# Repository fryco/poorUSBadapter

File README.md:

# poorUSBadapter
V-USB hardware adapter for `poorDuino`

## Features
* Comaptible with `poorDuino` and another Arduino-flavoured boards (pin compatibility with Arduino UNO R3 is kept),
* Differential pair routing is apllied to `D+` and `D-` signal traces,
* Bootloader button included into design.

## Resources
1. V-USB https://www.obdev.at/products/vusb/index.html
2. metaboard https://metalab.at/wiki/Metaboard

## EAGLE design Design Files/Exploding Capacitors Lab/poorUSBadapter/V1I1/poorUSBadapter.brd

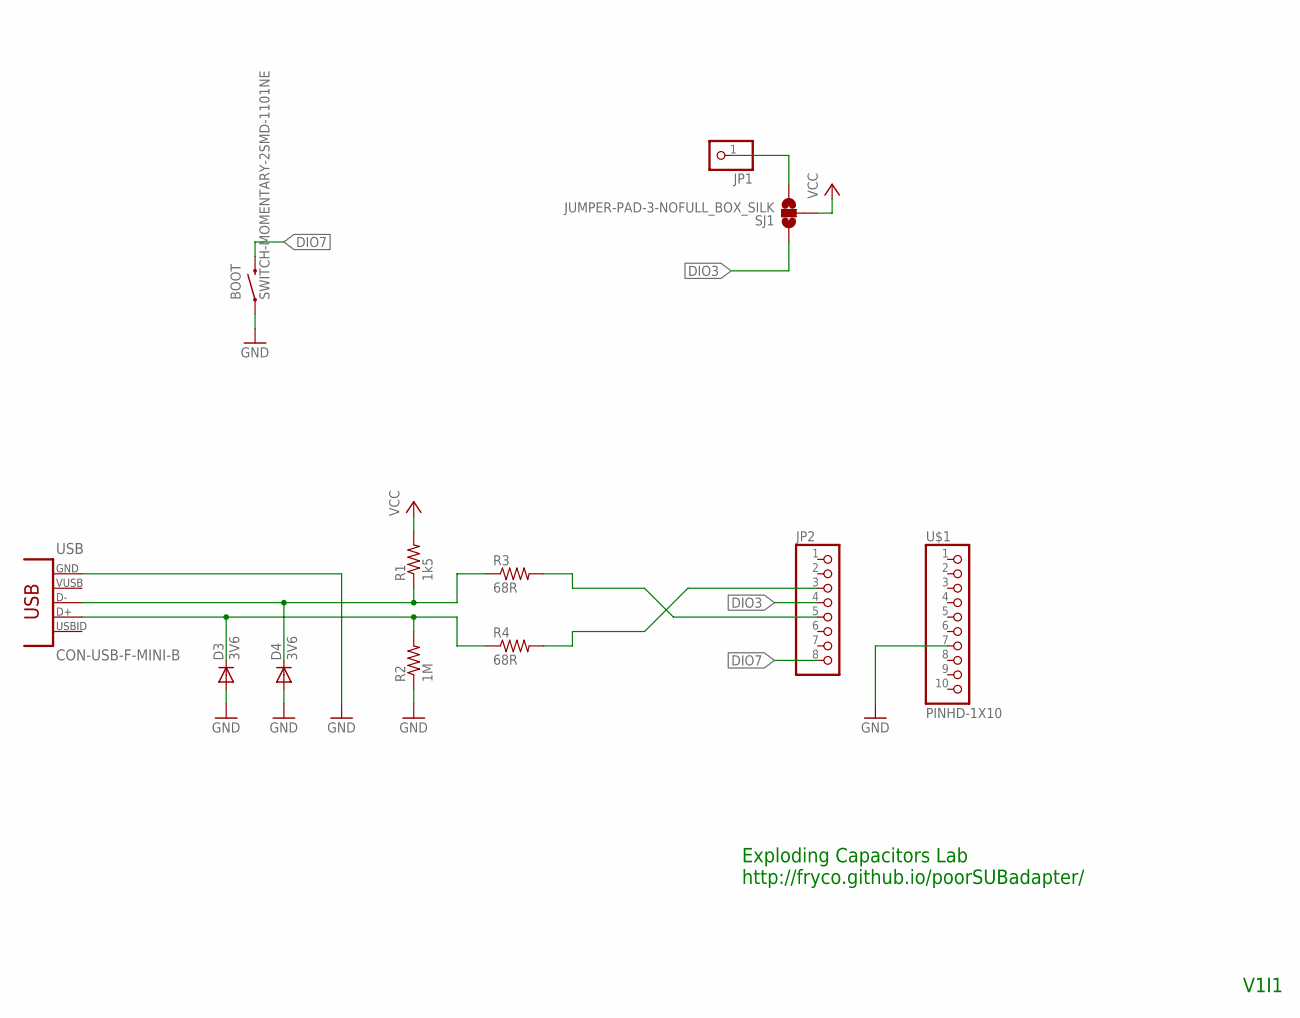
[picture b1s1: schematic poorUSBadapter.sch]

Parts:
BOOT: SWITCH-MOMENTARY-2SMD-1101NE; TACTILE-SWITCH-1101NE
D3, D4: 3V6; MICROMELF-W
JP1: PINHD-1X1; 1X01
JP2: PINHD-1X8BIG; 1X08-BIG
R1: 1k5; 0805
R2: 1M; 0805
R3, R4: 68R; 0805
SJ1: JUMPER-PAD-3-NOFULL_BOX_SILK; PAD-JUMPER-3-NO_YES_SILK_FULL_BOX
U$1: PINHD-1X10; 1X10-BIG
USB: CON-USB-F-MINI-B; CONN_USB_MINI-B

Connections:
DIO3: JP2.4, SJ1.1
DIO7: BOOT.2, JP2.8
GND: BOOT.1, D3.A, D4.A, R2.1, U$1.7, USB.GND
unnamed: JP1.1, SJ1.3
USB_N: D4.C, R1.1, R3.1, USB.D-
USB_P: D3.C, R2.2, R4.1, USB.D+
U_N: JP2.5, R3.2
U_P: JP2.3, R4.2
VCC: R1.2, SJ1.2

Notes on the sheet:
Exploding Capacitors Lab http://fryco.github.io/poorSUBadapter/
V1I1

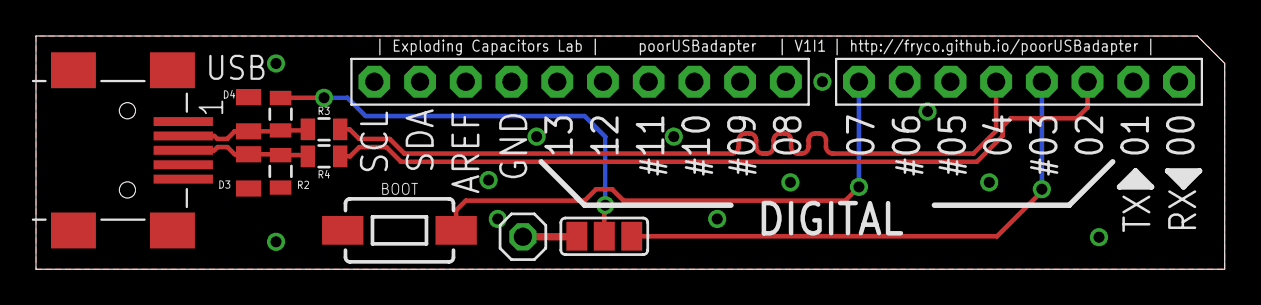
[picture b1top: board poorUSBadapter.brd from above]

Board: 2 copper layers, 66.0 x 13.0 mm, 12 parts (0 on the bottom side), 9 nets.

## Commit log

2015-08-21 :neckbeard: Added .gitattributes
2015-08-21 .gitignore update
2015-08-21 README.md update
2015-08-24 Schematic file was created
2015-08-24 Work files added - metaboard
2015-08-27 Schematic update
2015-08-27 PCB layout update
2015-08-27 Library update
2015-08-28 Zener diodes changed to microMELF, fixed connector size
2015-08-28 PCB layout almost done
2015-08-31 Create gh-pages branch via GitHub
2015-08-31 V1I1 is ready
2015-08-31 BackMeUp.py fix
2015-08-31 V1I1 is ready!
2015-08-31 Release files added!
2015-08-31 Release files added.
2015-08-31 Files and dirs cleanup.

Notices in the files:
parts and their libraries:
SparkFun-Passives: Licensing: Creative Commons ShareAlike 4.0 International - https://creativecommons.org/licenses/by-sa/4.0
